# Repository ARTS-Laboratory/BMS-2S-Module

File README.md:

# BMS-2S-Module
Generic BMS module for two cells in series

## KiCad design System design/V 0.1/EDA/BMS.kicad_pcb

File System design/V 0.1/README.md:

# V0.1

<p align="center">
Figure 1: PCB for V0.1

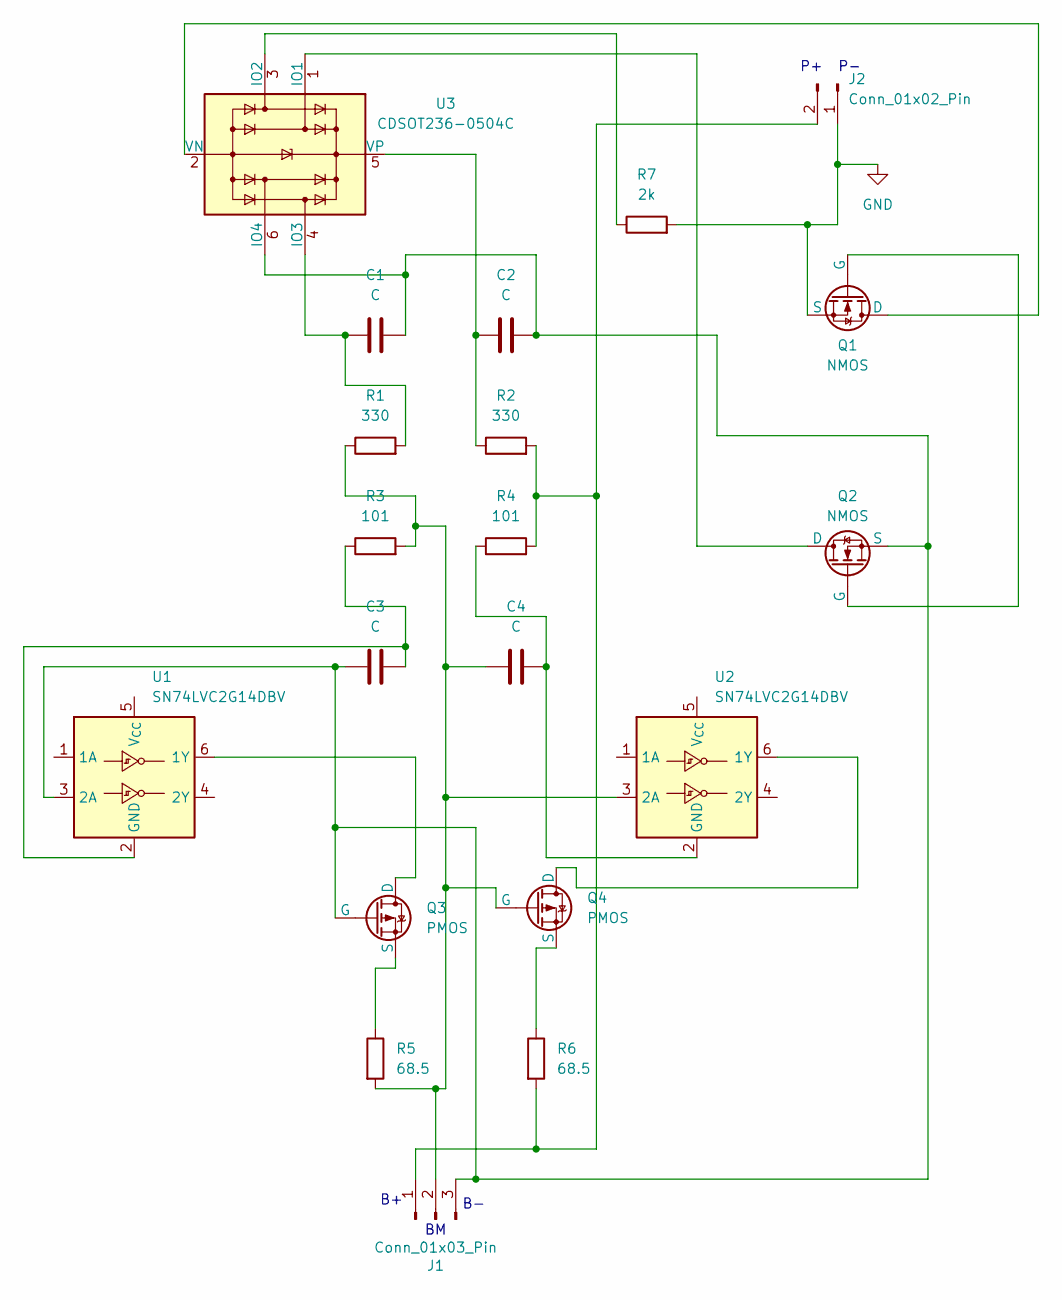
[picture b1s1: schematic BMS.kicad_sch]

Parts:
C1, C2, C3, C4: C; C_0603_1608Metric_Pad1.08x0.95mm_HandSolder
J1: Conn_01x03_Pin; JST_XH_B3B-XH-A_1x03_P2.50mm_Vertical
J2: Conn_01x02_Pin; JST_EH_B2B-EH-A_1x02_P2.50mm_Vertical
Q1, Q2: NMOS; TO-252-2
Q3, Q4: PMOS; SOT-23
R1, R2: 330; R_0603_1608Metric_Pad0.98x0.95mm_HandSolder
R3, R4: 101; R_0603_1608Metric_Pad0.98x0.95mm_HandSolder
R5, R6: 68.5; R_2512_6332Metric_Pad1.40x3.35mm_HandSolder
R7: 2k; R_0603_1608Metric_Pad0.98x0.95mm_HandSolder
U1, U2: SN74LVC2G14DBV; SOT-23-6
U3: CDSOT236-0504C; SOT-23-6

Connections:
GND: J2.1, Q1.3 (S), R7.2
unnamed: J1.1, J2.2, R2.2, R4.2, R6.2
unnamed: C4.1, J1.2, Q4.2 (G), R1.1, R3.2, R5.2, U2.3 (2A)
unnamed: C1.2, C2.2, C3.1, J1.3, Q2.3 (S), Q3.2 (G), U1.3 (2A), U3.6 (IO4)
unnamed: Q1.1 (D), U3.2 (VN)
unnamed: Q1.2 (G), Q2.2 (G)
unnamed: Q2.1 (D), U3.1 (IO1)
unnamed: Q3.1 (D), U1.6 (1Y)
unnamed: Q3.3 (S), R5.1
unnamed: Q4.1 (D), U2.6 (1Y)
unnamed: Q4.3 (S), R6.1
unnamed: C3.2, R3.1, U1.2 (GND)
unnamed: C4.2, R4.1, U2.2 (GND)
unnamed: R7.1, U3.3 (IO2)
unnamed: C1.1, R1.2, U3.4 (IO3)
unnamed: C2.1, R2.1, U3.5 (VP)

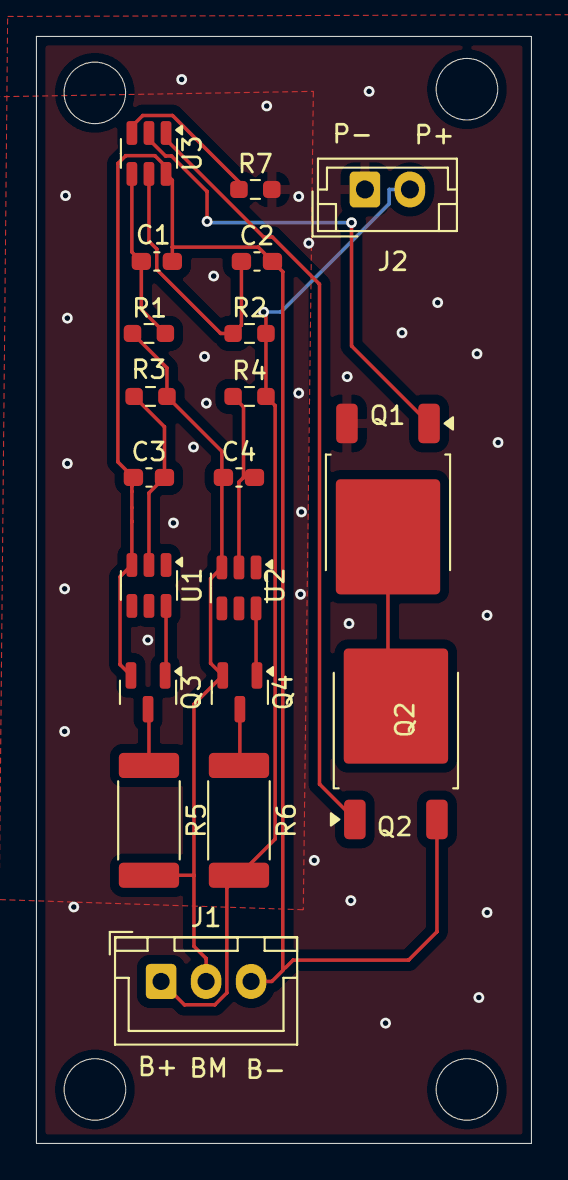
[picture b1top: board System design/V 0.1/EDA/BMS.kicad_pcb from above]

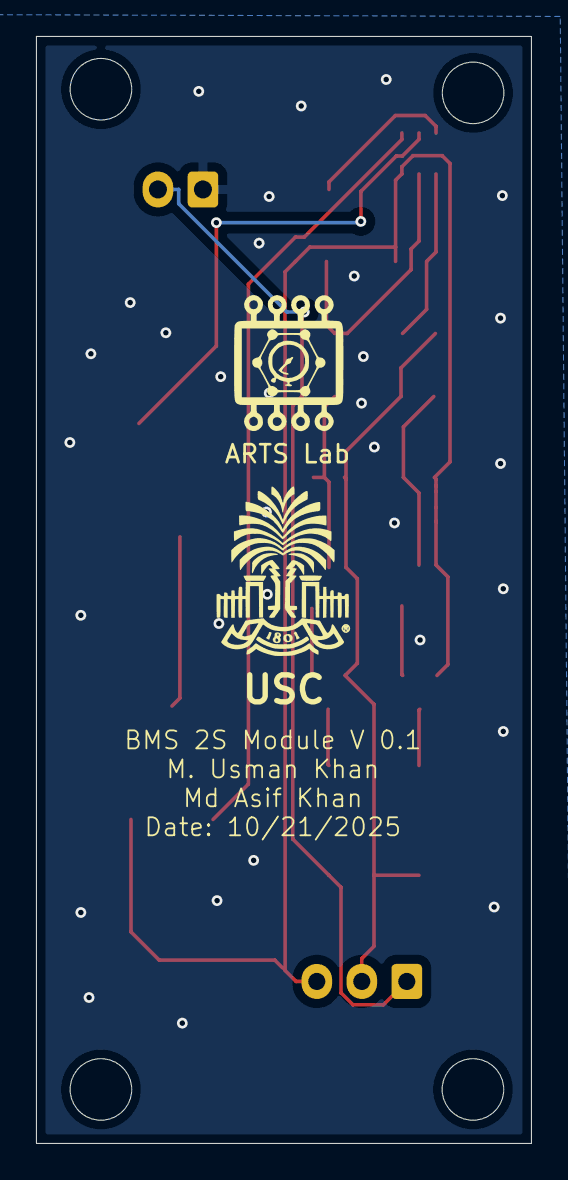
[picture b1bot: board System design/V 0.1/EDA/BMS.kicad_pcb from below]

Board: 2 copper layers, 27.5 x 61.5 mm, 22 parts (2 on the bottom side), 16 nets.

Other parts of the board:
ARTS Lab: LOGO
USC: UofSC; LOGO

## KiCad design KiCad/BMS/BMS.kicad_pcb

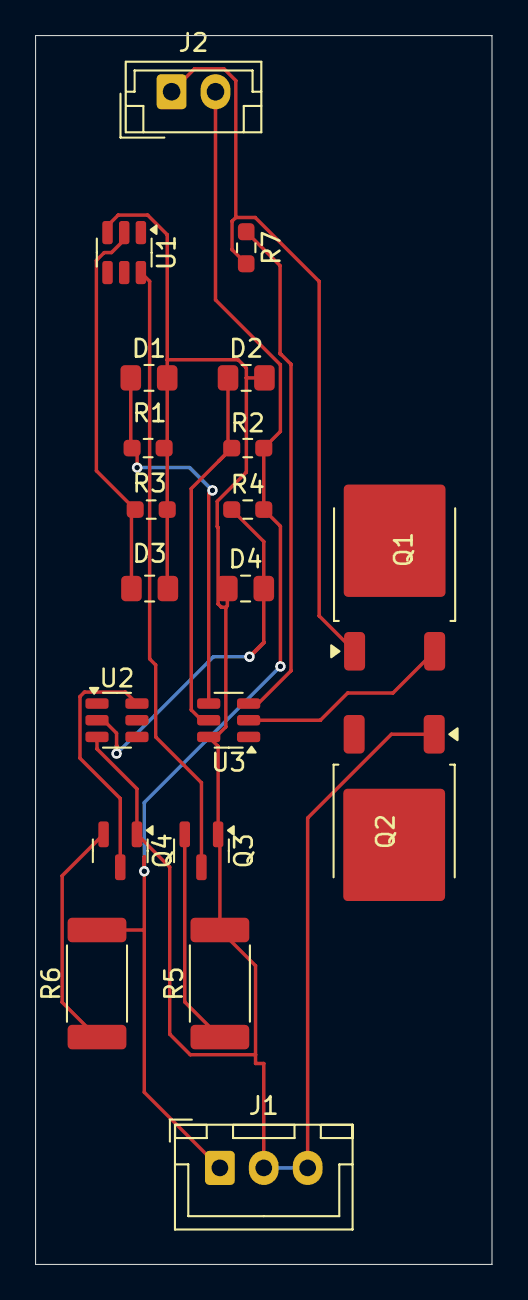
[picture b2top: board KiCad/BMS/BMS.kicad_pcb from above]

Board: 2 copper layers, 26.0 x 70.0 mm, 20 parts (0 on the bottom side), 13 nets.

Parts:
D1, D2, D3, D4: D_Capacitance; C_0805_2012Metric_Pad1.18x1.45mm_HandSolder
J1: Conn_01x03_Pin; JST_XH_B3B-XH-A_1x03_P2.50mm_Vertical
J2: Conn_01x02_Pin; JST_EH_B2B-EH-A_1x02_P2.50mm_Vertical
Q1, Q2: NMOS; TO-252-2
Q3, Q4: PMOS; SOT-23
R1, R2: 330; R_0603_1608Metric_Pad0.98x0.95mm_HandSolder
R3, R4: 101; R_0603_1608Metric_Pad0.98x0.95mm_HandSolder
R5, R6: 68.5; R_2512_6332Metric_Pad1.40x3.35mm_HandSolder
R7: 2k; R_0603_1608Metric_Pad0.98x0.95mm_HandSolder
U1, U2: SN74LVC2G14DBV; SOT-23-6
U3: CDSOT236-0504C; SOT-23-6

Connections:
unnamed: D1.2 (A), D2.2 (A), D3.1 (K), D4.1 (K), J1.2, J1.3, Q2.1 (D), Q3.1 (D), Q4.1 (D), R1.1, R3.2, R5.2, U1.3 (2A), U2.3 (2A), U3.6 (IO4)
unnamed: D1.1 (K), R1.2, U3.4 (IO3)
unnamed: D2.1 (K), R2.1, U3.5 (VP)
unnamed: D3.2 (A), R3.1, U1.2 (GND)
unnamed: D4.2 (A), R4.1, U2.2 (GND)
unnamed: J1.1, J2.2, R2.2, R4.2, R6.2
unnamed: J2.1, Q1.1 (D), R7.2
unnamed: Q1.3 (S), U3.2 (VN)
unnamed: Q3.2 (G), R5.1
unnamed: Q3.3 (S), U1.6 (1Y)
unnamed: Q4.2 (G), R6.1
unnamed: Q4.3 (S), U2.6 (1Y)
unnamed: R7.1, U3.3 (IO2)

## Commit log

2025-09-16 V 0.1 folder created
2025-09-25 added design considerations document
2025-10-03 BMS Module Connections
2025-10-03 KiCAD Model (Still Working)
2025-10-08 BMS_KiCAD Design (Final)
2025-10-13 Updated Directory
2025-10-13 kicad version number added
2025-10-13 removed all the backup files
2025-10-13 updated git ignore
2025-10-14 BMS Design Update
2025-10-14 Updated with latest corrections
2025-10-17 Version update
2025-10-17 Updated PCB (BMS)
2025-10-18 update gitignore for .lck files
2025-10-18 update gitignore
2025-10-21 PCB modified
2025-10-21 Design Updated
2025-10-22 Updated BMS Design
2025-10-22 Updated v0.1
2025-10-22 BMS Design Updated
2025-10-22 BMS Updated
2025-10-22 Figure Added
2025-10-23 Updated Readme file
2025-10-23 File Update
2025-10-23 eda code changed
2025-10-23 Gerber Files Created
2025-11-04 Gerber Files
2025-12-08 Update pads
